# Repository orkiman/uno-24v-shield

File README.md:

# uno-24v-shield

Arduino UNO 24V I/O shield, KiCad 9 project (v6).

* Outputs D8–D11: low-side N-MOSFET per channel (BSC0805LS) with flyback (SS56B + SMBJ15A to +24V) and drain-source TVS (SMBJ58A).
* Inputs D2–D5: 24V inputs through ULN2803 with indicator LEDs.
* RS232 on D0/D1: MAX232 + DB9 female (JP1 = RX jumper).
* 24V input: resettable fuse + TVS (surge / reverse polarity), 78M12 → Arduino VIN.

| Path | Content |
|---|---|
| `hardware/` | KiCad project (schematic, PCB, project symbol + footprint libraries) |
| `fab/` | JLCPCB order package: gerber zip, BOM, CPL |
| `docs/` | Schematic PDF, PCB PDF, renders, ERC/DRC reports, **REVIEW.md** (change list and checks) |
| `scripts/` | Generators: `design.py` (netlist source of truth), `gen_schematic.py`, `build_pcb.py`, `export_fab.py`, `check_polarity.py` |
| `source/easyeda/` | EasyEDA Pro backup of v5 that v6 is derived from |
| `source/lcsc/` | Cached LCSC/JLCPCB symbol pin names and footprints used for the footprint/polarity check |

Regenerate everything (KiCad 9 with its Python module required):

```
python3 scripts/build_pcb.py
python3 scripts/export_fab.py
```

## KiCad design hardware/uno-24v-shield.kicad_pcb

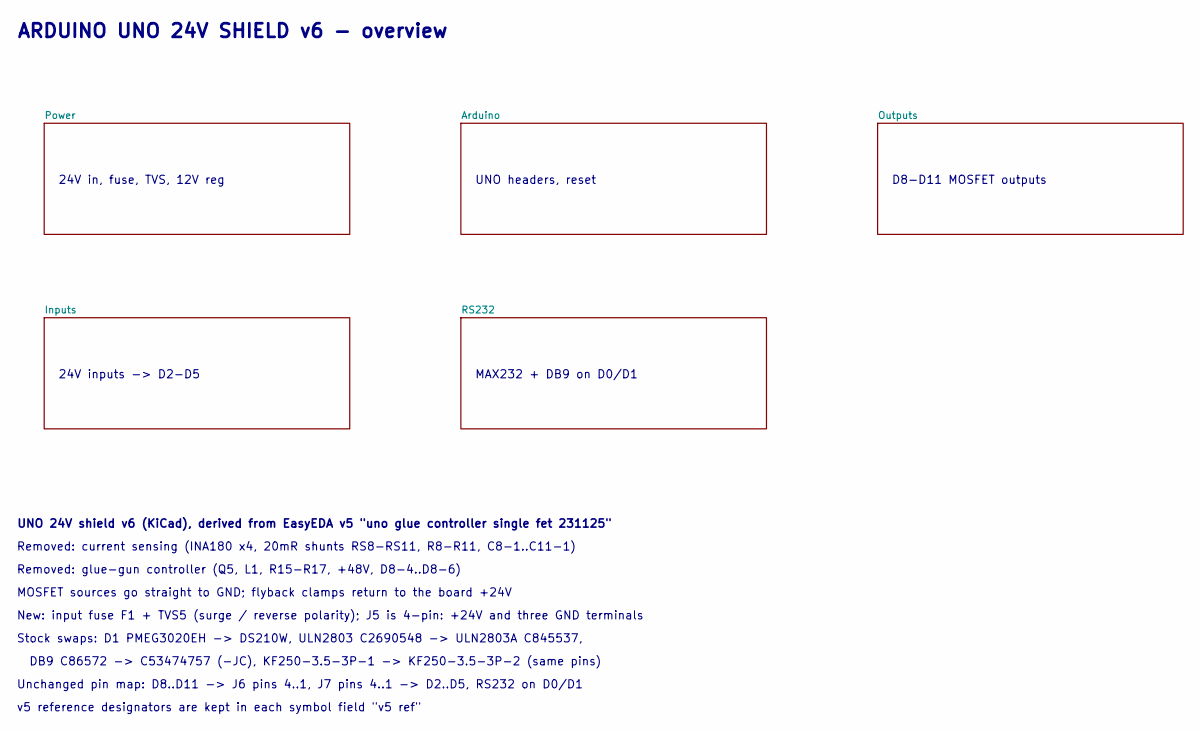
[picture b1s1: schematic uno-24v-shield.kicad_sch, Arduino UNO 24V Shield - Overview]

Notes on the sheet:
ARDUINO UNO 24V SHIELD v6 - overview
24V in, fuse, TVS, 12V reg
UNO headers, reset
D8-D11 MOSFET outputs
24V inputs -> D2-D5
MAX232 + DB9 on D0/D1
UNO 24V shield v6 (KiCad), derived from EasyEDA v5 "uno glue controller single fet 231125"
Removed: current sensing (INA180 x4, 20mR shunts RS8-RS11, R8-R11, C8-1..C11-1)
Removed: glue-gun controller (Q5, L1, R15-R17, +48V, D8-4..D8-6)
MOSFET sources go straight to GND; flyback clamps return to the board +24V
New: input fuse F1 + TVS5 (surge / reverse polarity); J5 is 4-pin: +24V and three GND terminals
Stock swaps: D1 PMEG3020EH -> DS210W, ULN2803 C2690548 -> ULN2803A C845537,
DB9 C86572 -> C53474757 (-JC), KF250-3.5-3P-1 -> KF250-3.5-3P-2 (same pins)
Unchanged pin map: D8..D11 -> J6 pins 4..1, J7 pins 4..1 -> D2..D5, RS232 on D0/D1
v5 reference designators are kept in each symbol field "v5 ref"

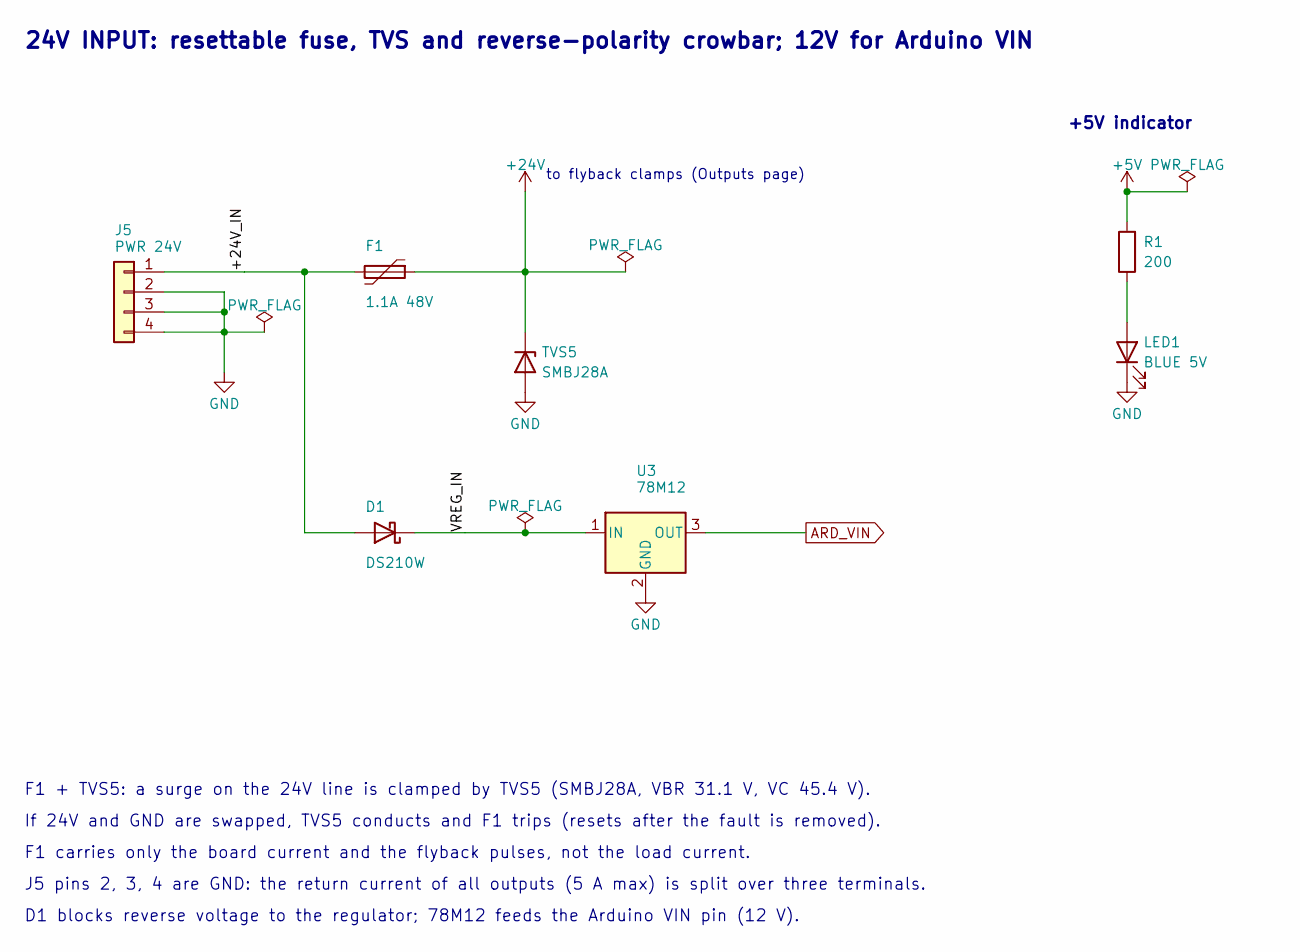
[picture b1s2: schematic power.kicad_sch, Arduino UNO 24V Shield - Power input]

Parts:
D1: DS210W; SOD-123FL_L2.7-W1.8-LS3.8-RD; MPN DS210W; LCSC C116100
F1: 1.1A 48V; F1812; MPN 1812L110/48QR; LCSC C19723490
J5: PWR 24V; CONN-TH_4P-P3.50_KF250-3.5-4P-1; MPN KF250-3.5-4P-1; LCSC C475156
LED1: BLUE 5V; LED0603-FD; MPN YLED0603B; LCSC C19171394
R1: 200; R0603; MPN 0603WAF2000T5E; LCSC C8218
TVS5: SMBJ28A; SMB_L4.3-W3.6-LS5.4-RD; MPN SMBJ28A; LCSC C113997
U3: 78M12; TO-252-2_L6.6-W6.1-P4.57-LS9.9-TL-CW; MPN 78M12; LCSC C116325

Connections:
+5V: R1.2; also elsewhere on the board
+24V: F1.1, TVS5.1 (K); also elsewhere on the board
/Power/+24V_IN: D1.2 (A), F1.2, J5.1
/Power/VREG_IN: D1.1 (K), U3.1 (IN)
ARD_VIN: U3.3 (OUT); also elsewhere on the board
GND: J5.2, J5.3, J5.4, LED1.2 (K), TVS5.2 (A), U3.2 (GND); also elsewhere on the board
unnamed: LED1.1 (A), R1.1

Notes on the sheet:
24V INPUT: resettable fuse, TVS and reverse-polarity crowbar; 12V for Arduino VIN
to flyback clamps (Outputs page)
+5V indicator
F1 + TVS5: a surge on the 24V line is clamped by TVS5 (SMBJ28A, VBR 31.1 V, VC 45.4 V).
If 24V and GND are swapped, TVS5 conducts and F1 trips (resets after the fault is removed).
F1 carries only the board current and the flyback pulses, not the load current.
J5 pins 2, 3, 4 are GND: the return current of all outputs (5 A max) is split over three terminals.
D1 blocks reverse voltage to the regulator; 78M12 feeds the Arduino VIN pin (12 V).

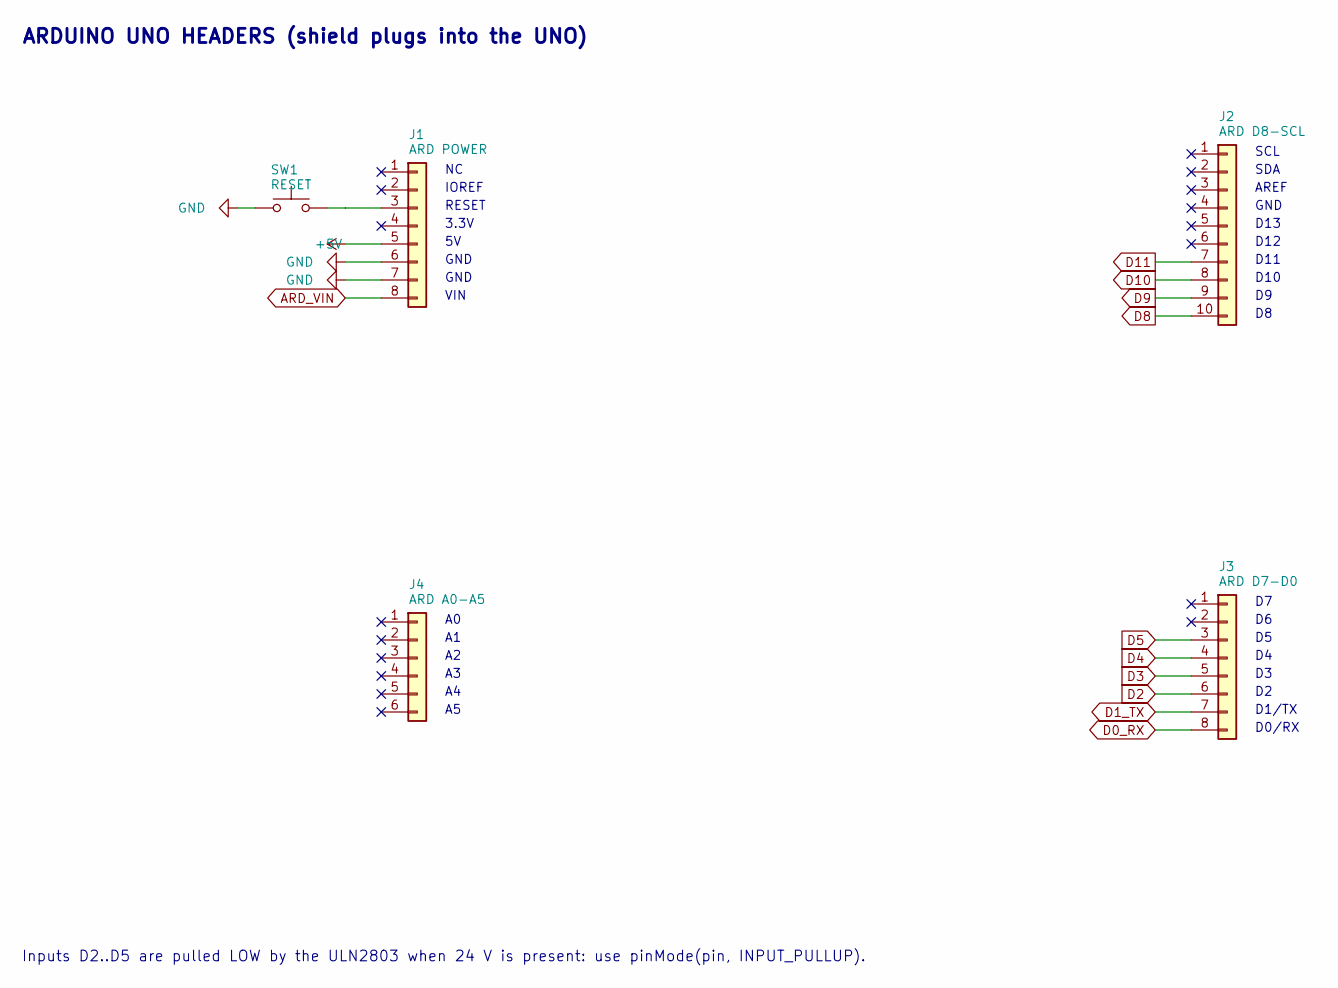
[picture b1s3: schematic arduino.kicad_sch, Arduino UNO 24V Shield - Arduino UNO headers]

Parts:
J1: ARD POWER; HDR-TH_8P-P2.54-H-M; MPN MTP125-1108S1; LCSC C358689
J2: ARD D8-SCL; HDR-TH_10P-P2.54-V-M-1; MPN Headers Pins2.54mm1*10P; LCSC C57369
J3: ARD D7-D0; HDR-TH_8P-P2.54-H-M; MPN MTP125-1108S1; LCSC C358689
J4: ARD A0-A5; HDR-TH_6P-P2.54-V-M-1; MPN 68000-406HLF; LCSC C178289
SW1: RESET; SW-SMD_L4.0-W2.9-LS5.0; MPN TS-1088-AR02016; LCSC C720477

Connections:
+5V: J1.5; also elsewhere on the board
ARD_VIN: J1.8; also elsewhere on the board
D0_RX: J3.8; also elsewhere on the board
D1_TX: J3.7; also elsewhere on the board
D2: J3.6; also elsewhere on the board
D3: J3.5; also elsewhere on the board
D4: J3.4; also elsewhere on the board
D5: J3.3; also elsewhere on the board
D8: J2.10; also elsewhere on the board
D9: J2.9; also elsewhere on the board
D10: J2.8; also elsewhere on the board
D11: J2.7; also elsewhere on the board
GND: J1.6, J1.7, SW1.1; also elsewhere on the board
unnamed: J1.3, SW1.2

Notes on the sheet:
ARDUINO UNO HEADERS (shield plugs into the UNO)
IOREF
RESET
3.3V
GND
VIN
SCL
SDA
AREF
D13
D12
D11
D10
D1/TX
D0/RX
Inputs D2..D5 are pulled LOW by the ULN2803 when 24 V is present: use pinMode(pin, INPUT_PULLUP).

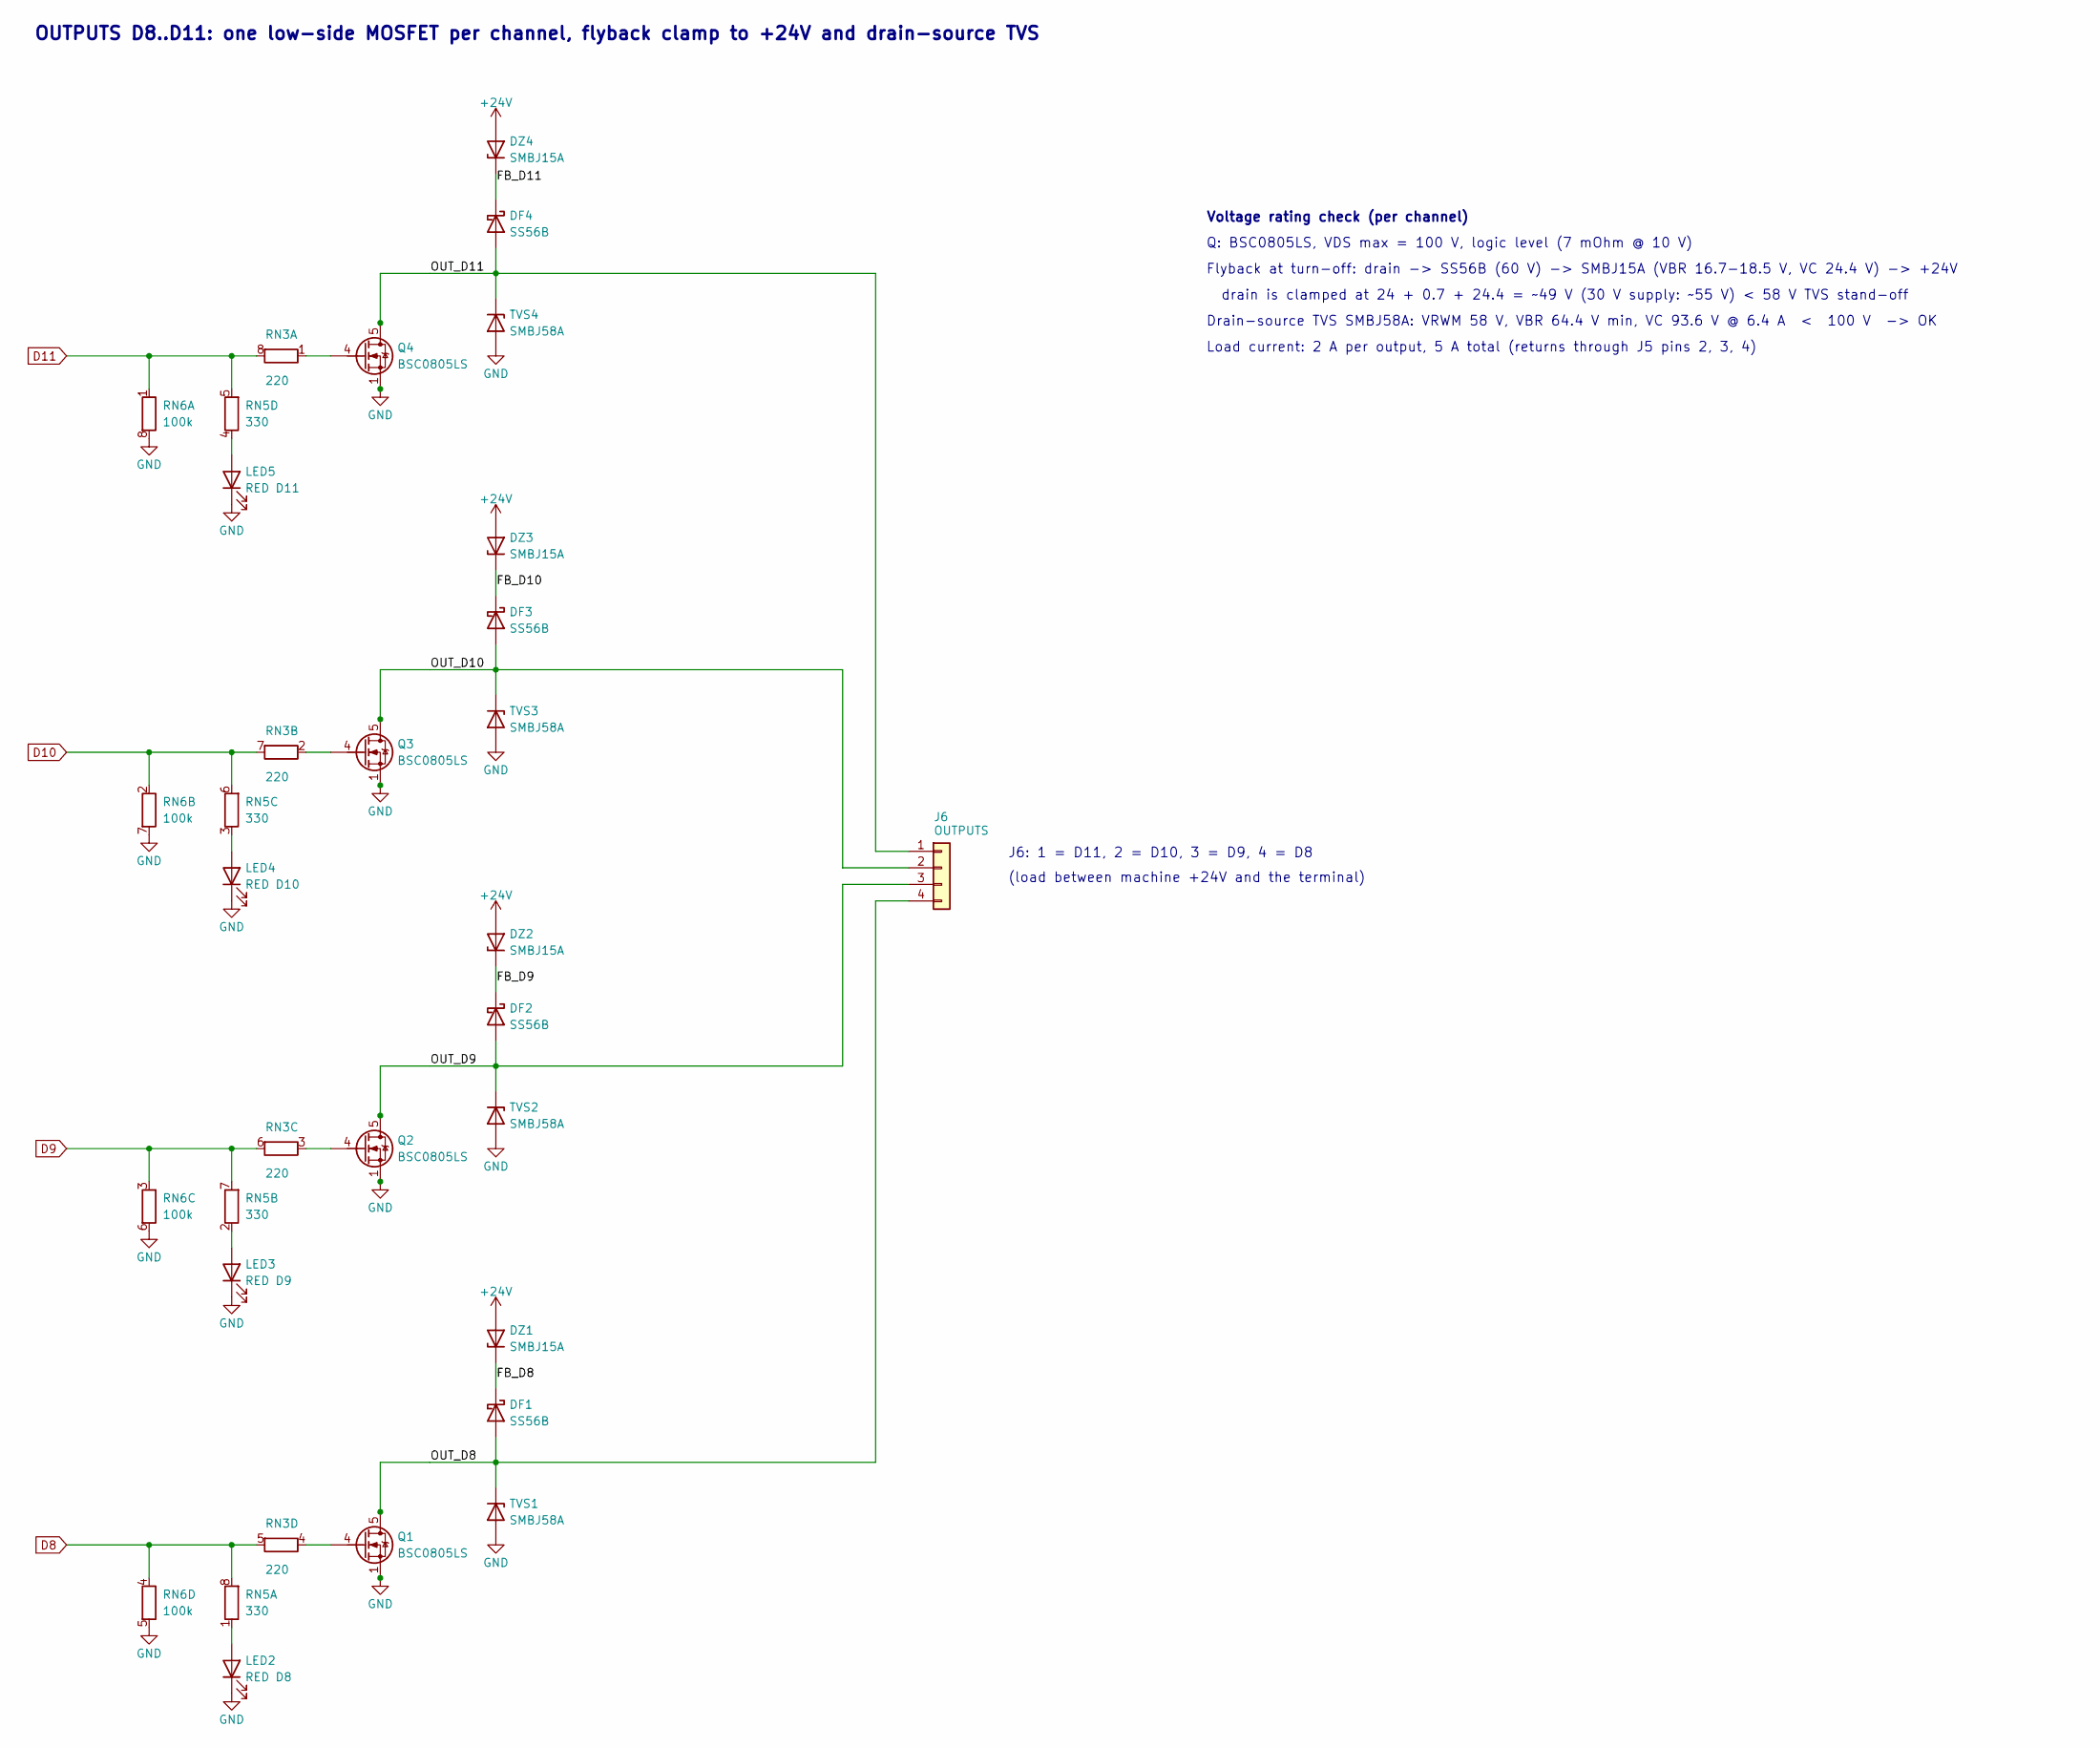
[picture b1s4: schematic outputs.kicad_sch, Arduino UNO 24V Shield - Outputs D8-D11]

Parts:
DF1, DF2, DF3, DF4: SS56B; SMB_L4.6-W3.7-LS5.4-RD; MPN SS56B; LCSC C5343335
DZ1, DZ2, DZ3, DZ4: SMBJ15A; SMB_L4.6-W3.6-LS5.3-RD; MPN SMBJ15A; LCSC C908796
J6: OUTPUTS; CONN-TH_4P-P3.50_KF250-3.5-4P-1; MPN KF250-3.5-4P-1; LCSC C475156
LED2: RED D8; LED0603-FD; MPN YLED0603R; LCSC C19171390
LED3: RED D9; LED0603-FD; MPN YLED0603R; LCSC C19171390
LED4: RED D10; LED0603-FD; MPN YLED0603R; LCSC C19171390
LED5: RED D11; LED0603-FD; MPN YLED0603R; LCSC C19171390
Q1, Q2, Q3, Q4: BSC0805LS; PG-TDSON-8_L5.2-W5.9-P1.27-LS6.2-BL-EP; MPN BSC0805LS; LCSC C534374
RN3: 220; RES-ARRAY-SMD_0402-8P-L2.0-W1.0-BL; MPN YC124-FR-07220RL; LCSC C728719
RN5: 330; RES-ARRAY-SMD_0402-8P-L2.0-W1.0-BL; MPN WA04X331JTL; LCSC C170189
RN6: 100k; RES-ARRAY-SMD_0402-8P-L2.0-W1.0-BL; MPN 4D02WGJ0104TCE; LCSC C25724
TVS1, TVS2, TVS3, TVS4: SMBJ58A; SMB_L4.6-W3.6-LS5.3-R-RD; MPN SMBJ58A; LCSC C41376102

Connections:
+24V: DZ1.2 (A), DZ2.2 (A), DZ3.2 (A), DZ4.2 (A); also elsewhere on the board
/Outputs/FB_D8: DF1.1 (K), DZ1.1 (K)
/Outputs/FB_D9: DF2.1 (K), DZ2.1 (K)
/Outputs/FB_D10: DF3.1 (K), DZ3.1 (K)
/Outputs/FB_D11: DF4.1 (K), DZ4.1 (K)
/Outputs/OUT_D8: DF1.2 (A), J6.4, Q1.5 (D), Q1.6 (D), Q1.7 (D), Q1.8 (D), Q1.9 (D), TVS1.2 (K)
/Outputs/OUT_D9: DF2.2 (A), J6.3, Q2.5 (D), Q2.6 (D), Q2.7 (D), Q2.8 (D), Q2.9 (D), TVS2.2 (K)
/Outputs/OUT_D10: DF3.2 (A), J6.2, Q3.5 (D), Q3.6 (D), Q3.7 (D), Q3.8 (D), Q3.9 (D), TVS3.2 (K)
/Outputs/OUT_D11: DF4.2 (A), J6.1, Q4.5 (D), Q4.6 (D), Q4.7 (D), Q4.8 (D), Q4.9 (D), TVS4.2 (K)
D8: RN3.5 (R4.2), RN5.8 (R1.2), RN6.4 (R4.1); also elsewhere on the board
D9: RN3.6 (R3.2), RN5.7 (R2.2), RN6.3 (R3.1); also elsewhere on the board
D10: RN3.7 (R2.2), RN5.6 (R3.2), RN6.2 (R2.1); also elsewhere on the board
D11: RN3.8 (R1.2), RN5.5 (R4.2), RN6.1 (R1.1); also elsewhere on the board
GND: LED2.2 (K), LED3.2 (K), LED4.2 (K), LED5.2 (K), Q1.1 (S), Q1.2 (S), Q1.3 (S), Q2.1 (S), Q2.2 (S), Q2.3 (S), Q3.1 (S), Q3.2 (S), Q3.3 (S), Q4.1 (S), Q4.2 (S), Q4.3 (S), RN6.5 (R4.2), RN6.6 (R3.2), RN6.7 (R2.2), RN6.8 (R1.2), TVS1.1 (A), TVS2.1 (A), TVS3.1 (A), TVS4.1 (A); also elsewhere on the board
unnamed: LED2.1 (A), RN5.1 (R1.1)
unnamed: LED3.1 (A), RN5.2 (R2.1)
unnamed: LED4.1 (A), RN5.3 (R3.1)
unnamed: LED5.1 (A), RN5.4 (R4.1)
unnamed: Q1.4 (G), RN3.4 (R4.1)
unnamed: Q2.4 (G), RN3.3 (R3.1)
unnamed: Q3.4 (G), RN3.2 (R2.1)
unnamed: Q4.4 (G), RN3.1 (R1.1)

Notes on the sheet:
OUTPUTS D8..D11: one low-side MOSFET per channel, flyback clamp to +24V and drain-source TVS
J6: 1 = D11, 2 = D10, 3 = D9, 4 = D8
(load between machine +24V and the terminal)
Voltage rating check (per channel)
Q: BSC0805LS, VDS max = 100 V, logic level (7 mOhm @ 10 V)
Flyback at turn-off: drain -> SS56B (60 V) -> SMBJ15A (VBR 16.7-18.5 V, VC 24.4 V) -> +24V
drain is clamped at 24 + 0.7 + 24.4 = ~49 V (30 V supply: ~55 V) < 58 V TVS stand-off
Drain-source TVS SMBJ58A: VRWM 58 V, VBR 64.4 V min, VC 93.6 V @ 6.4 A < 100 V -> OK
Load current: 2 A per output, 5 A total (returns through J5 pins 2, 3, 4)

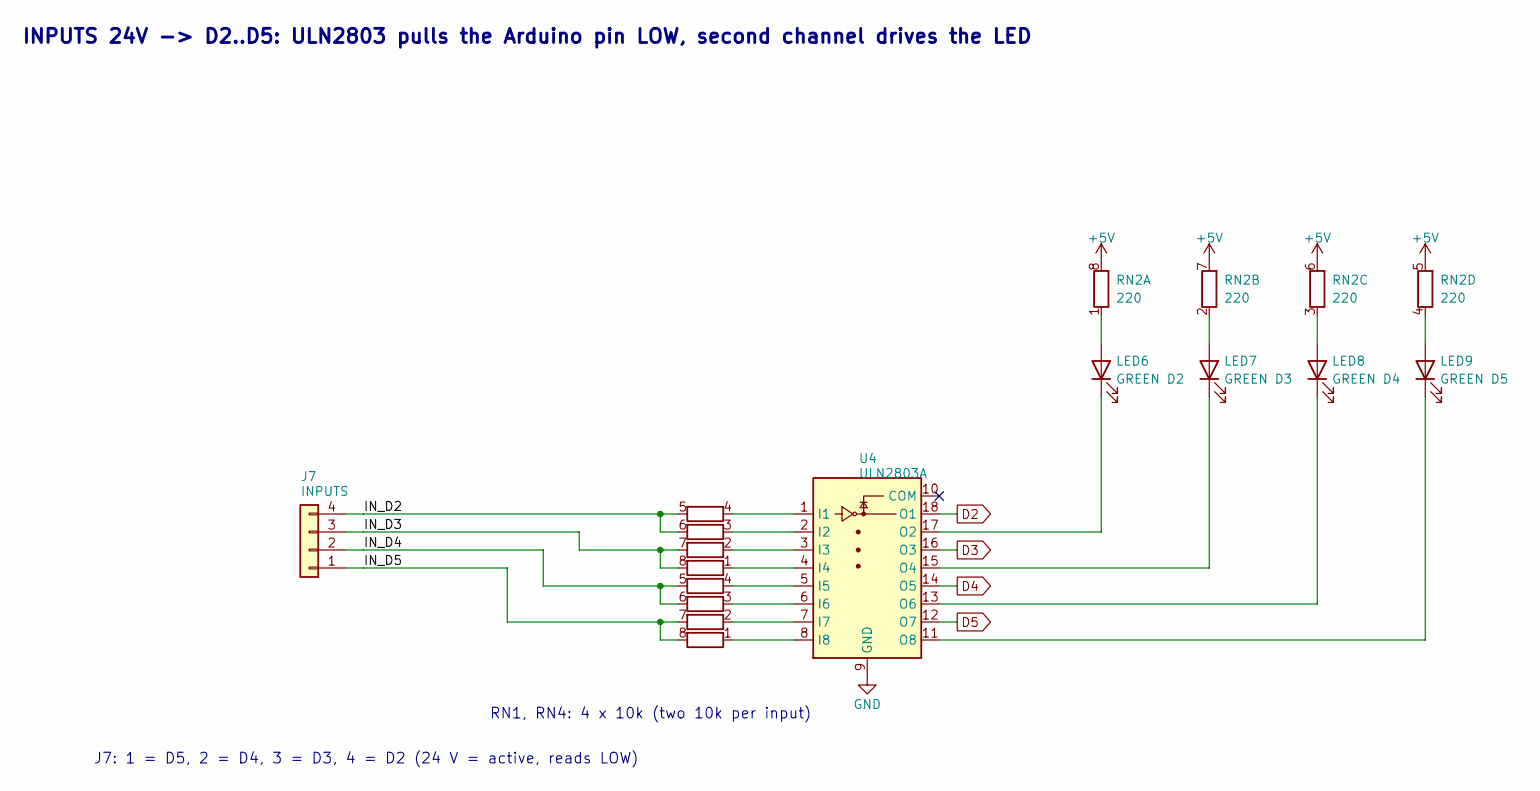
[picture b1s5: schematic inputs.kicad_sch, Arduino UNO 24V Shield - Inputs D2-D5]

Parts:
J7: INPUTS; CONN-TH_4P-P3.50_KF250-3.5-4P-1; MPN KF250-3.5-4P-1; LCSC C475156
LED6: GREEN D2; LED-SMD_L1.6-W0.8_19-219-GHC-YR2T1B5Y-3T; MPN 19-219/GHC-YR2T1B5Y/3T; LCSC C2994781
LED7: GREEN D3; LED-SMD_L1.6-W0.8_19-219-GHC-YR2T1B5Y-3T; MPN 19-219/GHC-YR2T1B5Y/3T; LCSC C2994781
LED8: GREEN D4; LED-SMD_L1.6-W0.8_19-219-GHC-YR2T1B5Y-3T; MPN 19-219/GHC-YR2T1B5Y/3T; LCSC C2994781
LED9: GREEN D5; LED-SMD_L1.6-W0.8_19-219-GHC-YR2T1B5Y-3T; MPN 19-219/GHC-YR2T1B5Y/3T; LCSC C2994781
RN1, RN4: 10k; RES-ARRAY-SMD_0603-8P-L3.2-W1.6-BL; MPN YC164-JR-0710KL; LCSC C107374
RN2: 220; RES-ARRAY-SMD_0603-8P-L3.2-W1.6-BL; MPN 4D03WGJ0221T5E; LCSC C29719
U4: ULN2803A; SOP-18_L11.4-W7.6-P1.27-LS10.6-BL; MPN ULN2803A; LCSC C845537

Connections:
+5V: RN2.5 (R4.2), RN2.6 (R3.2), RN2.7 (R2.2), RN2.8 (R1.2); also elsewhere on the board
/Inputs/IN_D2: J7.4, RN1.5 (R4.2), RN1.6 (R3.2)
/Inputs/IN_D3: J7.3, RN1.7 (R2.2), RN1.8 (R1.2)
/Inputs/IN_D4: J7.2, RN4.5 (R4.2), RN4.6 (R3.2)
/Inputs/IN_D5: J7.1, RN4.7 (R2.2), RN4.8 (R1.2)
D2: U4.18 (O1); also elsewhere on the board
D3: U4.16 (O3); also elsewhere on the board
D4: U4.14 (O5); also elsewhere on the board
D5: U4.12 (O7); also elsewhere on the board
GND: U4.9 (GND); also elsewhere on the board
unnamed: LED6.1 (A), RN2.1 (R1.1)
unnamed: LED6.2 (K), U4.17 (O2)
unnamed: LED7.1 (A), RN2.2 (R2.1)
unnamed: LED7.2 (K), U4.15 (O4)
unnamed: LED8.1 (A), RN2.3 (R3.1)
unnamed: LED8.2 (K), U4.13 (O6)
unnamed: LED9.1 (A), RN2.4 (R4.1)
unnamed: LED9.2 (K), U4.11 (O8)
unnamed: RN1.1 (R1.1), U4.4 (I4)
unnamed: RN1.2 (R2.1), U4.3 (I3)
unnamed: RN1.3 (R3.1), U4.2 (I2)
unnamed: RN1.4 (R4.1), U4.1 (I1)
unnamed: RN4.1 (R1.1), U4.8 (I8)
unnamed: RN4.2 (R2.1), U4.7 (I7)
unnamed: RN4.3 (R3.1), U4.6 (I6)
unnamed: RN4.4 (R4.1), U4.5 (I5)

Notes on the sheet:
INPUTS 24V -> D2..D5: ULN2803 pulls the Arduino pin LOW, second channel drives the LED
J7: 1 = D5, 2 = D4, 3 = D3, 4 = D2 (24 V = active, reads LOW)
RN1, RN4: 4 x 10k (two 10k per input)

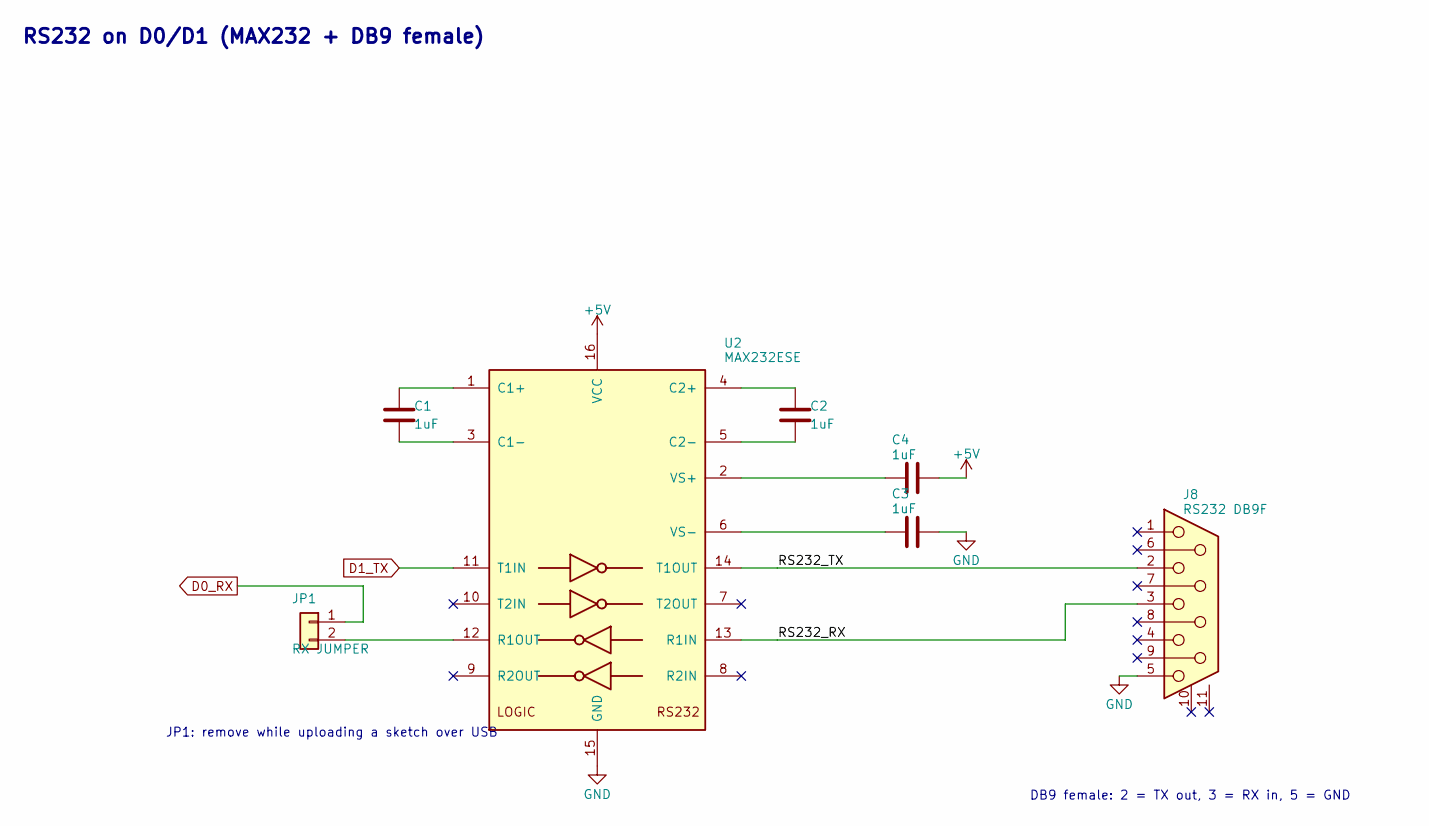
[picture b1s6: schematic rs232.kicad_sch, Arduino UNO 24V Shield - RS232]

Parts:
C1, C2, C3, C4: 1uF; C0603; MPN CL10A105KO8NNNC; LCSC C1592
J8: RS232 DB9F; DSUB-TH_DS1034-01-09FBN044; MPN DS1034-01-09FBN044-JC; LCSC C53474757
JP1: RX JUMPER; HDR-TH_2P-P2.54-V-M-1; MPN 22-28-4020; LCSC C234182
U2: MAX232ESE; SOIC-16_L9.9-W3.9-P1.27-LS6.0-BL; MPN MAX232ESE+T; LCSC C26860

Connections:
+5V: C4.2, U2.16 (VCC); also elsewhere on the board
/RS232/RS232_RX: J8.3, U2.13 (R1IN)
/RS232/RS232_TX: J8.2, U2.14 (T1OUT)
D0_RX: JP1.1; also elsewhere on the board
D1_TX: U2.11 (T1IN); also elsewhere on the board
GND: C3.1, J8.5, U2.15 (GND); also elsewhere on the board
unnamed: JP1.2, U2.12 (R1OUT)
unnamed: C1.2, U2.1 (C1+)
unnamed: C1.1, U2.3 (C1-)
unnamed: C2.2, U2.4 (C2+)
unnamed: C2.1, U2.5 (C2-)
unnamed: C4.1, U2.2 (VS+)
unnamed: C3.2, U2.6 (VS-)

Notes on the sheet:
RS232 on D0/D1 (MAX232 + DB9 female)
JP1: remove while uploading a sketch over USB
DB9 female: 2 = TX out, 3 = RX in, 5 = GND

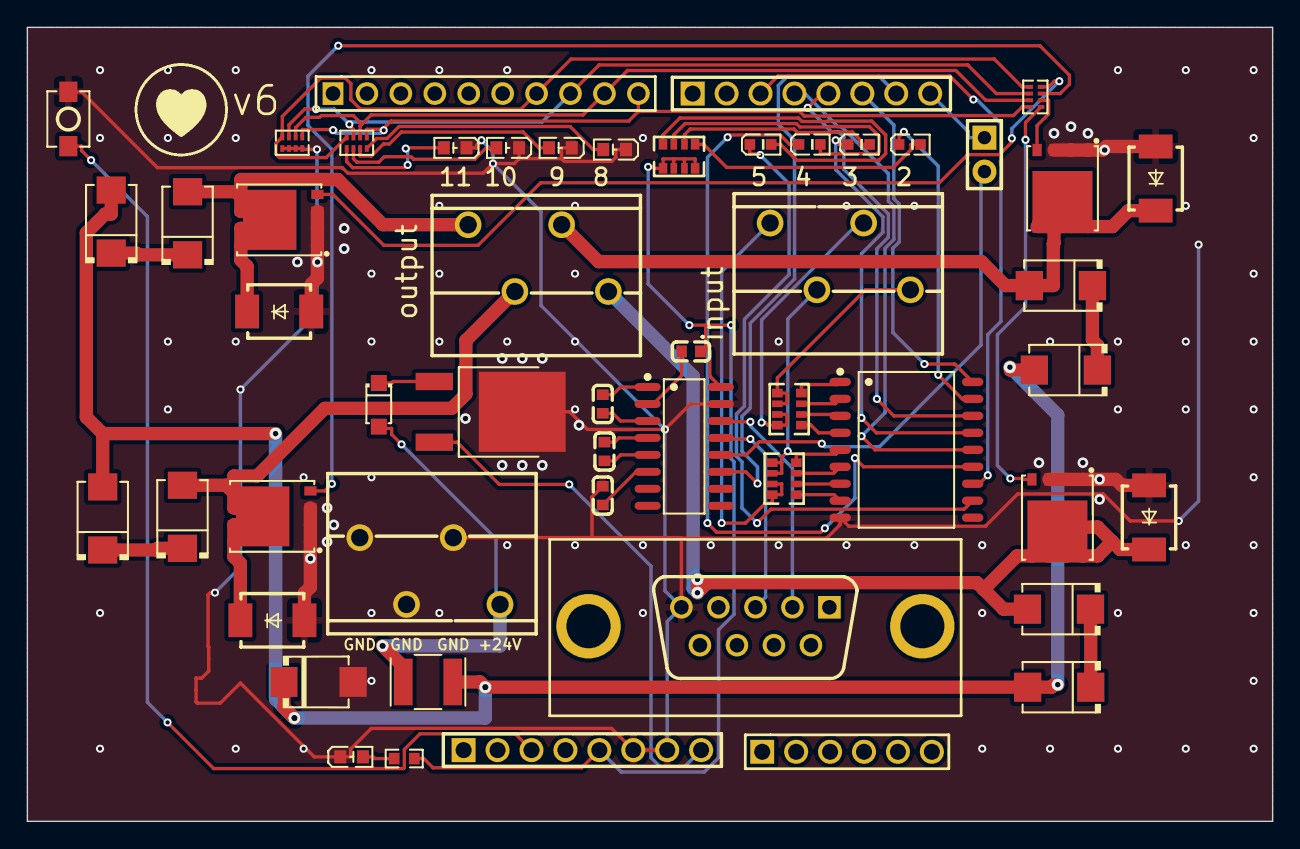
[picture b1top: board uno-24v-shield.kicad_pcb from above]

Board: 2 copper layers, 93.2 x 59.4 mm, 52 parts (0 on the bottom side), 63 nets.

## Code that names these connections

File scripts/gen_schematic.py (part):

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
Layout: a root overview page plus one page per functional block.  Inside a
block everything is connected with real wires; only signals that travel
between pages use global labels (D2..D11, D0_RX, D1_TX, ARD_VIN) and the
power nets use power symbols.

The drawing is checked three ways: every pin must land on a wire end, label,
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    u3 = pg.place('U3', 99.06, yR)
    nodeV = (83.82, yR)
    pg.wire(d1.pin(1), nodeV, u3.pin(1))
    pg.label('VREG_IN', (76.2, yR), (0, -1))
    pg.power('PWR_FLAG', nodeV)
    pg.power('GND', u3.pin(2))
    pg.wire(u3.pin(3), (119.38, yR))
    pg.glabel('ARD_VIN', (119.38, yR), (1, 0), 'output')
    # 5V indicator
    pg.text('+5V indicator', 152.4, 40.64, 1.5, True)
    x5 = 160.02
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    # TX
    p = u2.pin(11)
    pg.wire(p, (p[0] - 7.62, p[1]))
    pg.glabel('D1_TX', (p[0] - 7.62, p[1]), (-1, 0), 'input')
    # RX through jumper JP1
    jp = pg.place('JP1', 60.96, 111.76, mirror=True)
    pg.wire(jp.pin(2), u2.pin(12))
    a = jp.pin(1)
    pg.wire(a, (a[0] + 2.54, a[1]), (a[0] + 2.54, 106.68), (50.8, 106.68))
    pg.glabel('D0_RX', (50.8, 106.68), (-1, 0), 'output')
    pg.text('JP1: remove while uploading a sketch over USB', 40.64, 128.27, 1.27)
    # DB9
    j8 = pg.place('J8', 185.42, 109.22)
    t = u2.pin(14)
    pg.wire(t, j8.pin(2))
    pg.label('RS232_TX', (t[0] + 5.08, t[1]), (1, 0))
    rr = u2.pin(13)
    pg.wire(rr, (167.64, rr[1]), (167.64, j8.pin(3)[1]), j8.pin(3))
    pg.label('RS232_RX', (rr[0] + 5.08, rr[1]), (1, 0))
    g = j8.pin(5)
    pg.wire(g, (g[0] - 2.54, g[1]))
    pg.power('GND', (g[0] - 2.54, g[1]))
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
